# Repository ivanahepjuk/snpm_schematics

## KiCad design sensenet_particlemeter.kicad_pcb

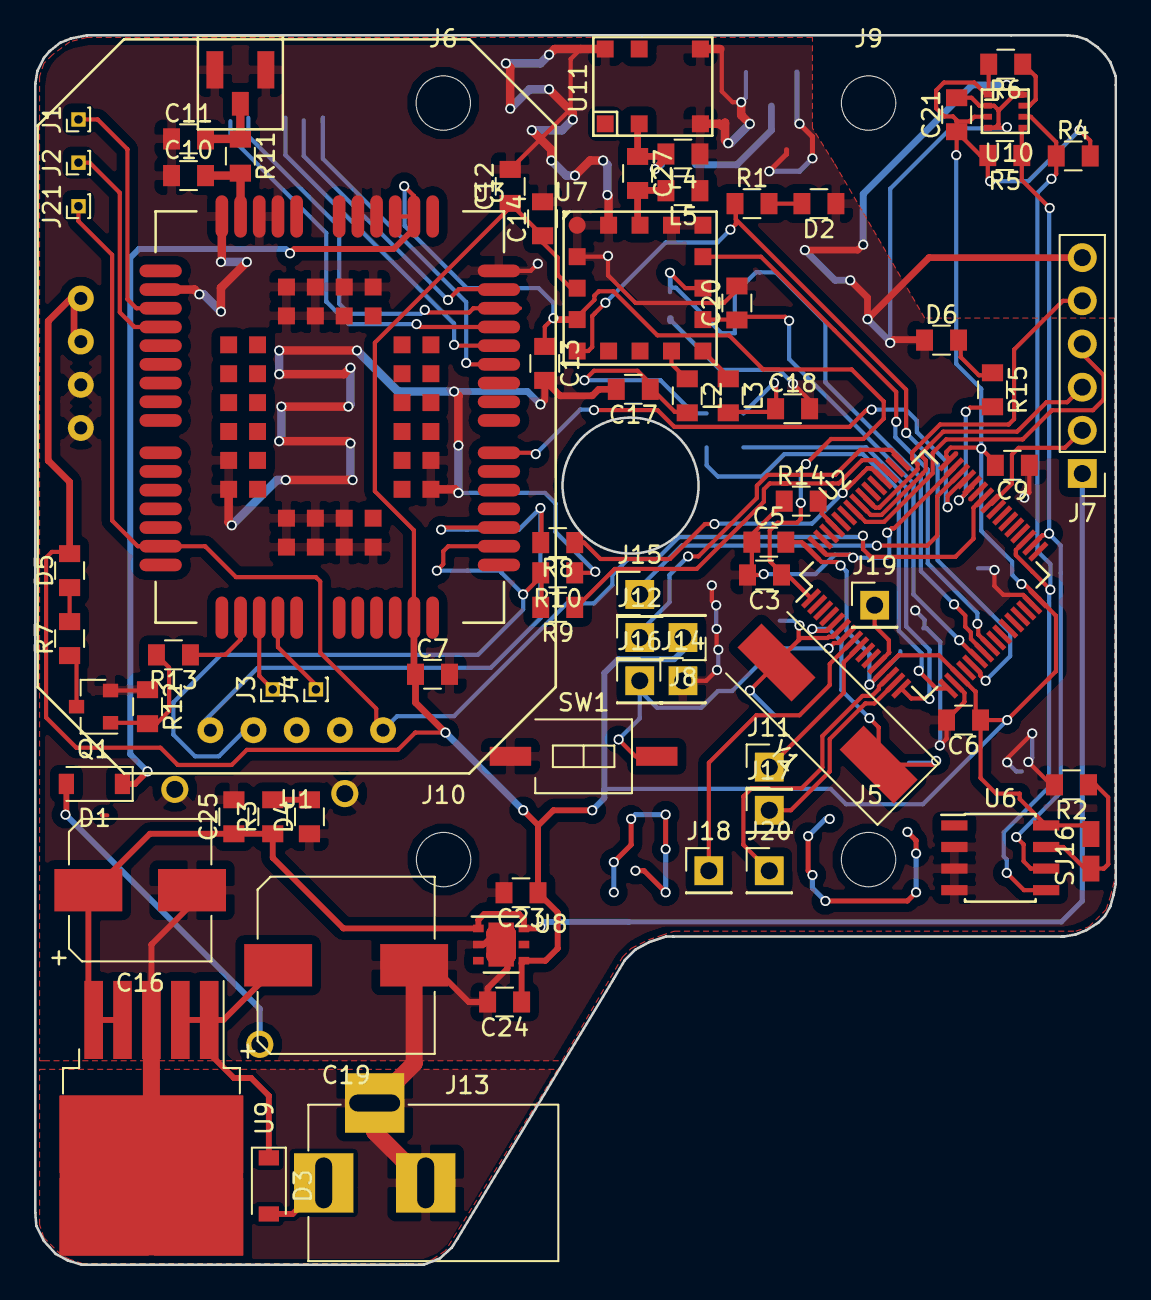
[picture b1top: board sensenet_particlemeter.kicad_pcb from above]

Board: 2 copper layers, 63.6 x 72.3 mm, 91 parts (0 on the bottom side), 64 nets.

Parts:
BT1: Battery_Cell; BAT-CR2032_bottom
C1, C2: 4.3p; SMD_0805_bottom
C3, C6, C9, C27: C; SMD_0805
C4, C8: C; SMD_0805_bottom
C5, C7, C21: 100n; SMD_0805
C10, C11: NC; SMD_0805
C12, C13, C17, C18, C20: 22p; SMD_0805
C14: 2,2u; SMD_0805
C16: 220n; CP_Elec_8x10
C19: 470u; CP_Elec_10x10
C22: 22p; SMD_0805_bottom
C23, C25: 10u; SMD_0805
C24: 220n; SMD_0805
D1: D_Schottky; D_SOD-123
D2, D4, D5, D6: LED; SMD_0805
D3: D_Schottky_ss14; D_SOD-123
J1, J2, J3, J4, J21: CONN_01X01; Pin_Header_Straight_1x01_Pitch1.00mm
J5, J6, J9, J10: CONN_01X01; MountingHole_3.2mm_M3_DIN965
J7: CONN_01X06; Pin_Header_Straight_1x06_Pitch2.54mm
J8, J11, J12, J14, J15, J16, J17, J18, J19, J20: CONN_01X01; Pin_Header_Straight_1x01_Pitch2.54mm
J13: BARREL_JACK
L2, L3: 47n; SMD_0805
L4, L5: L; SMD_0805
P1: SMA_mini; Antenna_conn
P2: SMA_mini; Antenna_conn_bott
Q1: Q_NPN_BCV71; SOT-23
R1: R; SMD_0805
R2, R4, R5, R13: 4.7k; SMD_0805
R3: 5k6; SMD_0805
R6: 22k; SMD_0805
R7, R8, R9, R15: 1k; SMD_0805
R10, R14: 10k; SMD_0805
R11: 0R; SMD_0805
R12: 47k; SMD_0805
SJ1, SJ15, SJ17: solder_jumper; solder_jumper_bott
SJ16: solder_jumper
SW1: SW_Push; SW_DIP_x1_W8.61mm_Slide_SMD_LowProfile
U1: wireless_patice; wireless_footprint
U2: stm32f072; TQFP-64_10x10mm_Pitch0.5mm
U3: QUECTEL_BC95; quectel_BC95
U4: SIM; nanosim_bottom
U6: M24C04; SOIC-8_3.9x4.9mm_Pitch1.27mm
U7: M10578-A2; M10578
U8: LD39050; DFN-6-1EP_3x3mm_Pitch0.95mm
U9: NCP59150; TO-263-5_TabPin3
U10: bme280_barebone; BME280
U11: SR4G008
Y1: 8MHz; Crystal_SMD_HC49-SD

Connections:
+3V3: C4.1, C5.2, C6.1, C7.1, C8.1, C9.2, C12.1, C14.1, C21.1, C23.1, C24.1, D5.2, J8.1, R4.2, R5.2, R6.2, SJ16.2, U1.1, U1.2, U2.13, U2.19, U2.32, U2.48, U2.64, U3.26, U6.8, U7.15, U8.4, U10.1, U10.3
+5V: C16.1, C25.1, J7.1, R3.1, U8.1, U8.6, U9.4, U9.5
GND: BT1.2, BT1.3, C1.2, C2.2, C3.2, C4.2, C5.1, C6.2, C7.2, C8.2, C9.1, C10.1, C11.1, C12.2, C13.2, C14.2, C16.2, C17.2, C18.2, C19.2, C20.2, C21.2, C22.2, C23.2, C24.2, C25.2, D2.1, D4.1, D6.1, J7.6, J13.2, J13.3, J14.1, L4.1, L5.1, P1.1, P1.3, P2.1, P2.3, Q1.2, R2.2, R10.1, R12.1, R14.1, SW1.1, U1.3, U1.4, U2.18, U2.31, U2.47, U2.63, U3.2, U3.43, U3.47, U3.48, U3.51, U3.52, U3.54, U3.59, U3.60, U3.61, U3.62, U3.63, U3.64, U3.65, U3.66, U3.71, U3.72, U3.73, U3.74, U3.81, U3.82, U3.83, U3.92, U3.93, U3.94, U6.2, U6.3, U6.4, U7.1, U7.2, U7.4, U7.5, U7.16, U8.2, U8.7, U9.3, U10.2, U10.4, U10.8, U11.3, U11.4, U11.6
unnamed: BT1.1, D1.2
unnamed: C1.1, U2.5, Y1.1
unnamed: C2.1, U2.6, Y1.2
unnamed: C10.2, R11.2, U3.53
unnamed: C11.2, P1.2, R11.1
unnamed: C17.1, L2.2, SJ15.2
unnamed: C18.1, L3.2, SJ17.2
unnamed: C19.1, D3.1, U9.1, U9.2
unnamed: C27.1, L4.2, SJ1.1, U11.2
unnamed: D2.2, R1.2
unnamed: D3.2, J13.1
unnamed: D4.2, R3.2
unnamed: D5.1, R7.2
unnamed: D6.2, R15.1
unnamed: J1.1, U3.3
unnamed: J2.1, U3.4
unnamed: J3.1, U3.19
unnamed: J4.1, U3.20
unnamed: J11.1, U2.9
unnamed: J17.1, U2.15
unnamed: J18.1, U2.8
unnamed: J19.1, U2.12
unnamed: J20.1, U2.14
unnamed: L2.1, U7.10
unnamed: L3.1, U7.9
unnamed: P2.2, SJ1.2
unnamed: Q1.1, R12.2, R13.2
unnamed: Q1.3, R7.1
unnamed: R2.1, SJ16.1, U6.7
unnamed: R6.1, U10.7
unnamed: R8.2, U1.5, U3.30
unnamed: R9.2, R10.2, U1.6, U3.29
unnamed: R13.1, U3.18
unnamed: R14.2, U2.60
unnamed: R15.2, U2.44
unnamed: U3.38, U4.6
unnamed: U3.39, U4.4
unnamed: U3.40, U4.1
unnamed: U3.41, U4.2
unnamed: U3.42, U4.5
PM_SCK: J7.5, U2.55
PM_SDI: J7.4, U2.57
PM_SDO: J7.3, U2.56
PM_SS: J7.2, U2.41
RI: U2.45, U3.34
Rx: R8.1, U2.52
SWD_CLK: J12.1, U2.49
SWD_DIO: J15.1, U2.46
Tx: R9.1, U2.51
UART_GPS_RX: SJ15.1, U2.17
UART_GPS_TX: SJ17.1, U2.16
WIRELESS_reset: J21.1, U1.9, U2.42, U3.15
antenna: C27.2, L5.2, U7.3
batt: C3.1, C13.1, D1.1, U2.1, U3.45, U3.46, U7.14
gps_fix: R1.1, U2.21, U7.13
gps_pulses: U2.24, U7.6
gps_reset: C22.1, U2.23, U7.7
gps_standby: C20.1, U2.22, U7.8
i2c_scl: R5.1, U2.34, U6.6, U10.5
i2c_sda: R4.1, U2.35, U6.5, U10.6
reset: J16.1, SW1.2, U2.7

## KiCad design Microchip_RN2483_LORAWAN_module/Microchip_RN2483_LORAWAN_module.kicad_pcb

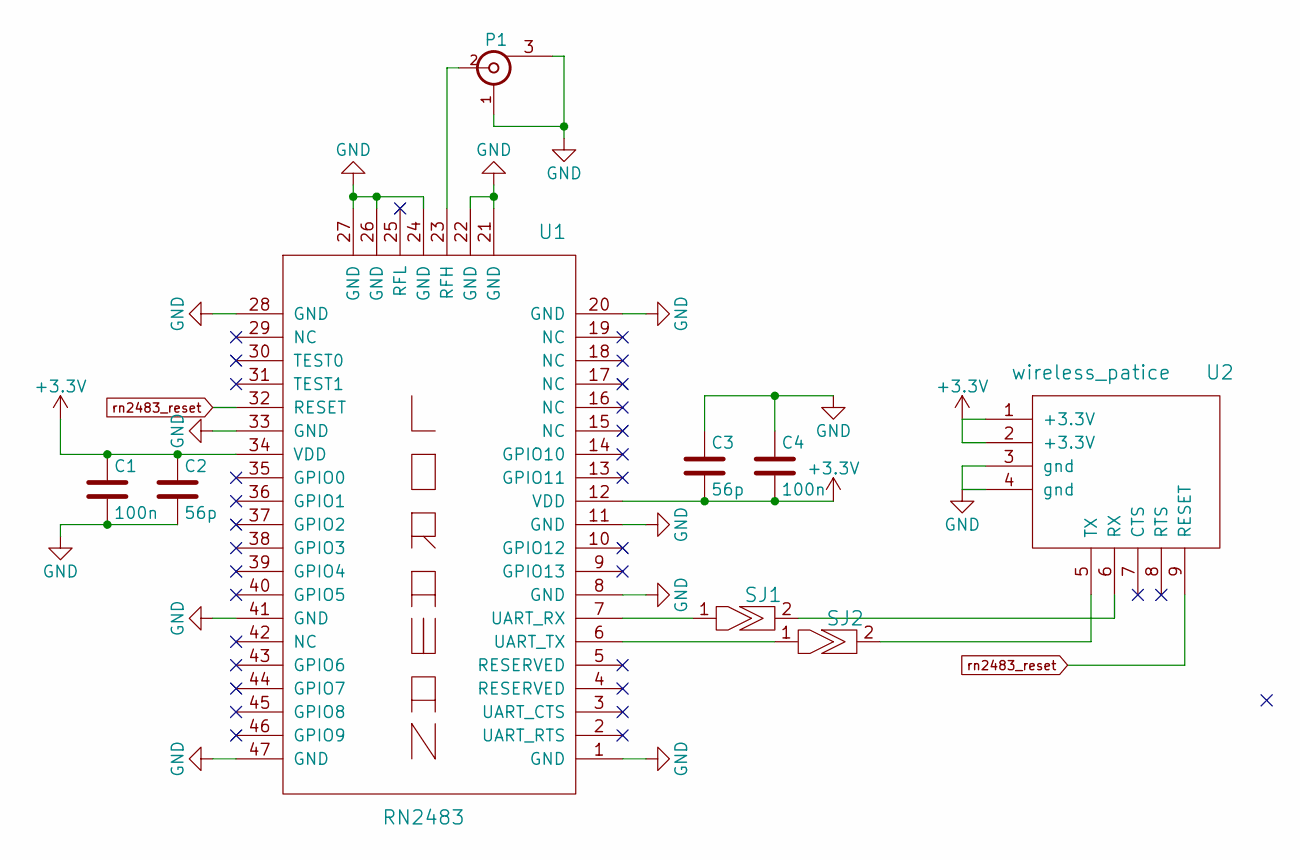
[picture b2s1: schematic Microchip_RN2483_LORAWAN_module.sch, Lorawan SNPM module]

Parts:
C1, C4: 100n; SMD_0805
C2, C3: 56p; SMD_0805
P1: SMA_mini; sma_conn
SJ1, SJ2: solder_jumper; solder_jumper_bott
U1: RN2483; RN2483_top
U2: wireless_patice; wireless_footprint

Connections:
+3V3: C1.1, C2.1, C3.2, C4.2, U1.12 (VDD), U1.34 (VDD), U2.1 (+3.3V), U2.2 (+3.3V)
GND: C1.2, C2.2, C3.1, C4.1, P1.1 (gnd), P1.3 (gnd), U1.1 (GND), U1.8 (GND), U1.11 (GND), U1.20 (GND), U1.21 (GND), U1.22 (GND), U1.24 (GND), U1.26 (GND), U1.27 (GND), U1.28 (GND), U1.33 (GND), U1.41 (GND), U1.47 (GND), U2.3 (gnd), U2.4 (gnd)
unnamed: P1.2 (In), U1.23 (RFH)
unnamed: SJ1.1, U1.7 (UART_RX)
unnamed: SJ1.2, U2.6 (RX)
unnamed: SJ2.1, U1.6 (UART_TX)
unnamed: SJ2.2, U2.5 (TX)
rn2483_reset: U1.32 (RESET), U2.9 (RESET)

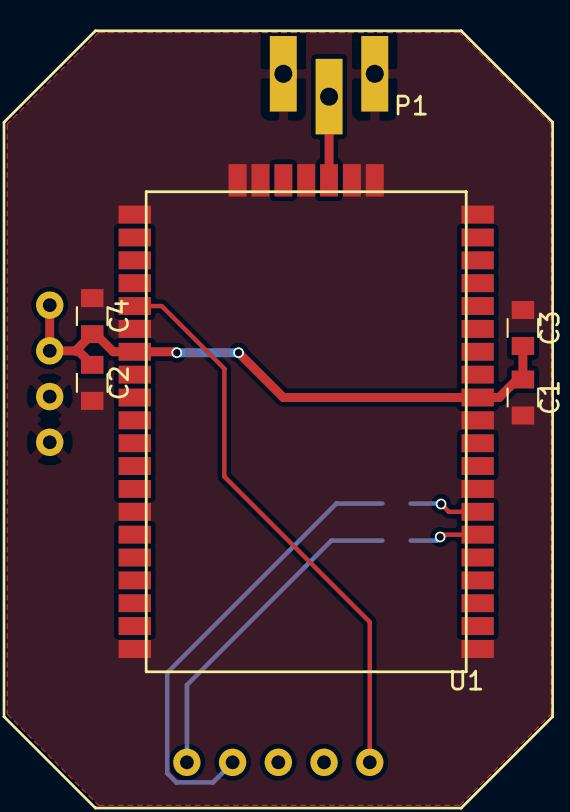
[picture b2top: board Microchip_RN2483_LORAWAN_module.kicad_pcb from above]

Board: 2 copper layers, 9 parts (0 on the bottom side), 8 nets.

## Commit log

2017-11-22 initial
2017-11-22 added reset pin wire for quectel, fixed holes position
2017-11-22 lorawan module PCB added
2017-11-22 lorawan module PCB added, reorganized folders
2017-11-22 reorganized power connections
2017-12-05 objednavka snpm a microchip redukce
